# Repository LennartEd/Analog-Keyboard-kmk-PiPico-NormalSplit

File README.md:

# Analog-Keyboard-kmk-PiPico-NormalSplit
This is a fully analog keyboard using magnetic keys and hall sensors. I'm using a RP2040 but since it is KMK (circuitpython) based it should be compatible with other boards. I build a split keyboard, but any type form factor should work. 
This is my first experience with circuitpython so code might me wonky.

#TO-DO
- [ ] automatic callibration
- [ ] support all types of multiplexers (not just 16:1)
- [ ] fix mouse wheel only pressing every second turn

# PCB
**!DONT USE THE PCB PROVIDED!**
The PCB provided has some flaws that make it hard to work with.
**I would recommend making your own PCB and using mine as a template.**
In the future i might create v2 template that fixes the flaws.
Also as LCSC didn't have the LEDs in stock, I build mine without them. So there is no guaranty that I did the LED wiring correctly. I did however test the code with the onboard led of the RP2040, so the code should work.

### Flaws with v1
- Horizontal encoder has the wrong footprint (gnd is not in the middle)
- dont solder MCU daughter board onto PCB directly
- bigger pads for hand soldering
- more mounting holes
- if possible 2 layer PCB for cost saving

### Parts
|Description | Part          | LCSC         |
|:-----------| ------------- |:-------------|
| Hall sensor| HX6659ISO-B   | C495742		|
| Multiplexer| CD74HC4067M96 | C496123		|
| TRRS jack  | PJ-3220-5A	 | C707251		|
| MCU		 | Waveshare RP2040-zero| --	|
| ~~Capacitor 100uF~~| ~~GRM21BR60J107ME15L~~| ~~C141660~~|
|(LED)       |sk6812 mini-e  | C5149201     |

### Part notes
**Hall sensor:** 

**Multiplexer:** Currently any 16to1 Multiplexer should work (giving you 64 keys). If you are not hand soldering i recommend choosing a smaller sized one. Larger (32to1) should also work.

**MCU:** Any circuitpython compatible board should work. You just have to change the footprint on the PCB (which you should do anyway. See "Flaws with v1"

**TRRS jack:** 

**Capacitor:** Capacitors are not strictly necessary but improve resolution. ~~I tried a few and found that 100uF worked the best.~~ Use different sensor filters

#### How it works
The position of the magnet in the switch is red by the hall-effect sensor. Because the pi-pico only has 4 ADCs we need multiplexers to cycle between the sensors. 

# Code
To install the code connect your board and install circuitpython. Then copy the content of the "code" folder into the board. For editing the code you can use Thonny or any text editor.

### pins
To make life easier by not having to use "board.GP.." all the time, create (if not already present) a python file in lib/kmk/quickpin. Then add all the pins (see the other files for reference).
Now when imported with 
~~~
from kmk.quickpin.<boardTypeFolder>.<boardPins> import pinout as pins
~~~
into other files you can just use "pins[x]" to reference pins

### kb.py:
Here you define most variables for you specific board.

### Code.py

### hallCali.py

### analogio.py

# Case

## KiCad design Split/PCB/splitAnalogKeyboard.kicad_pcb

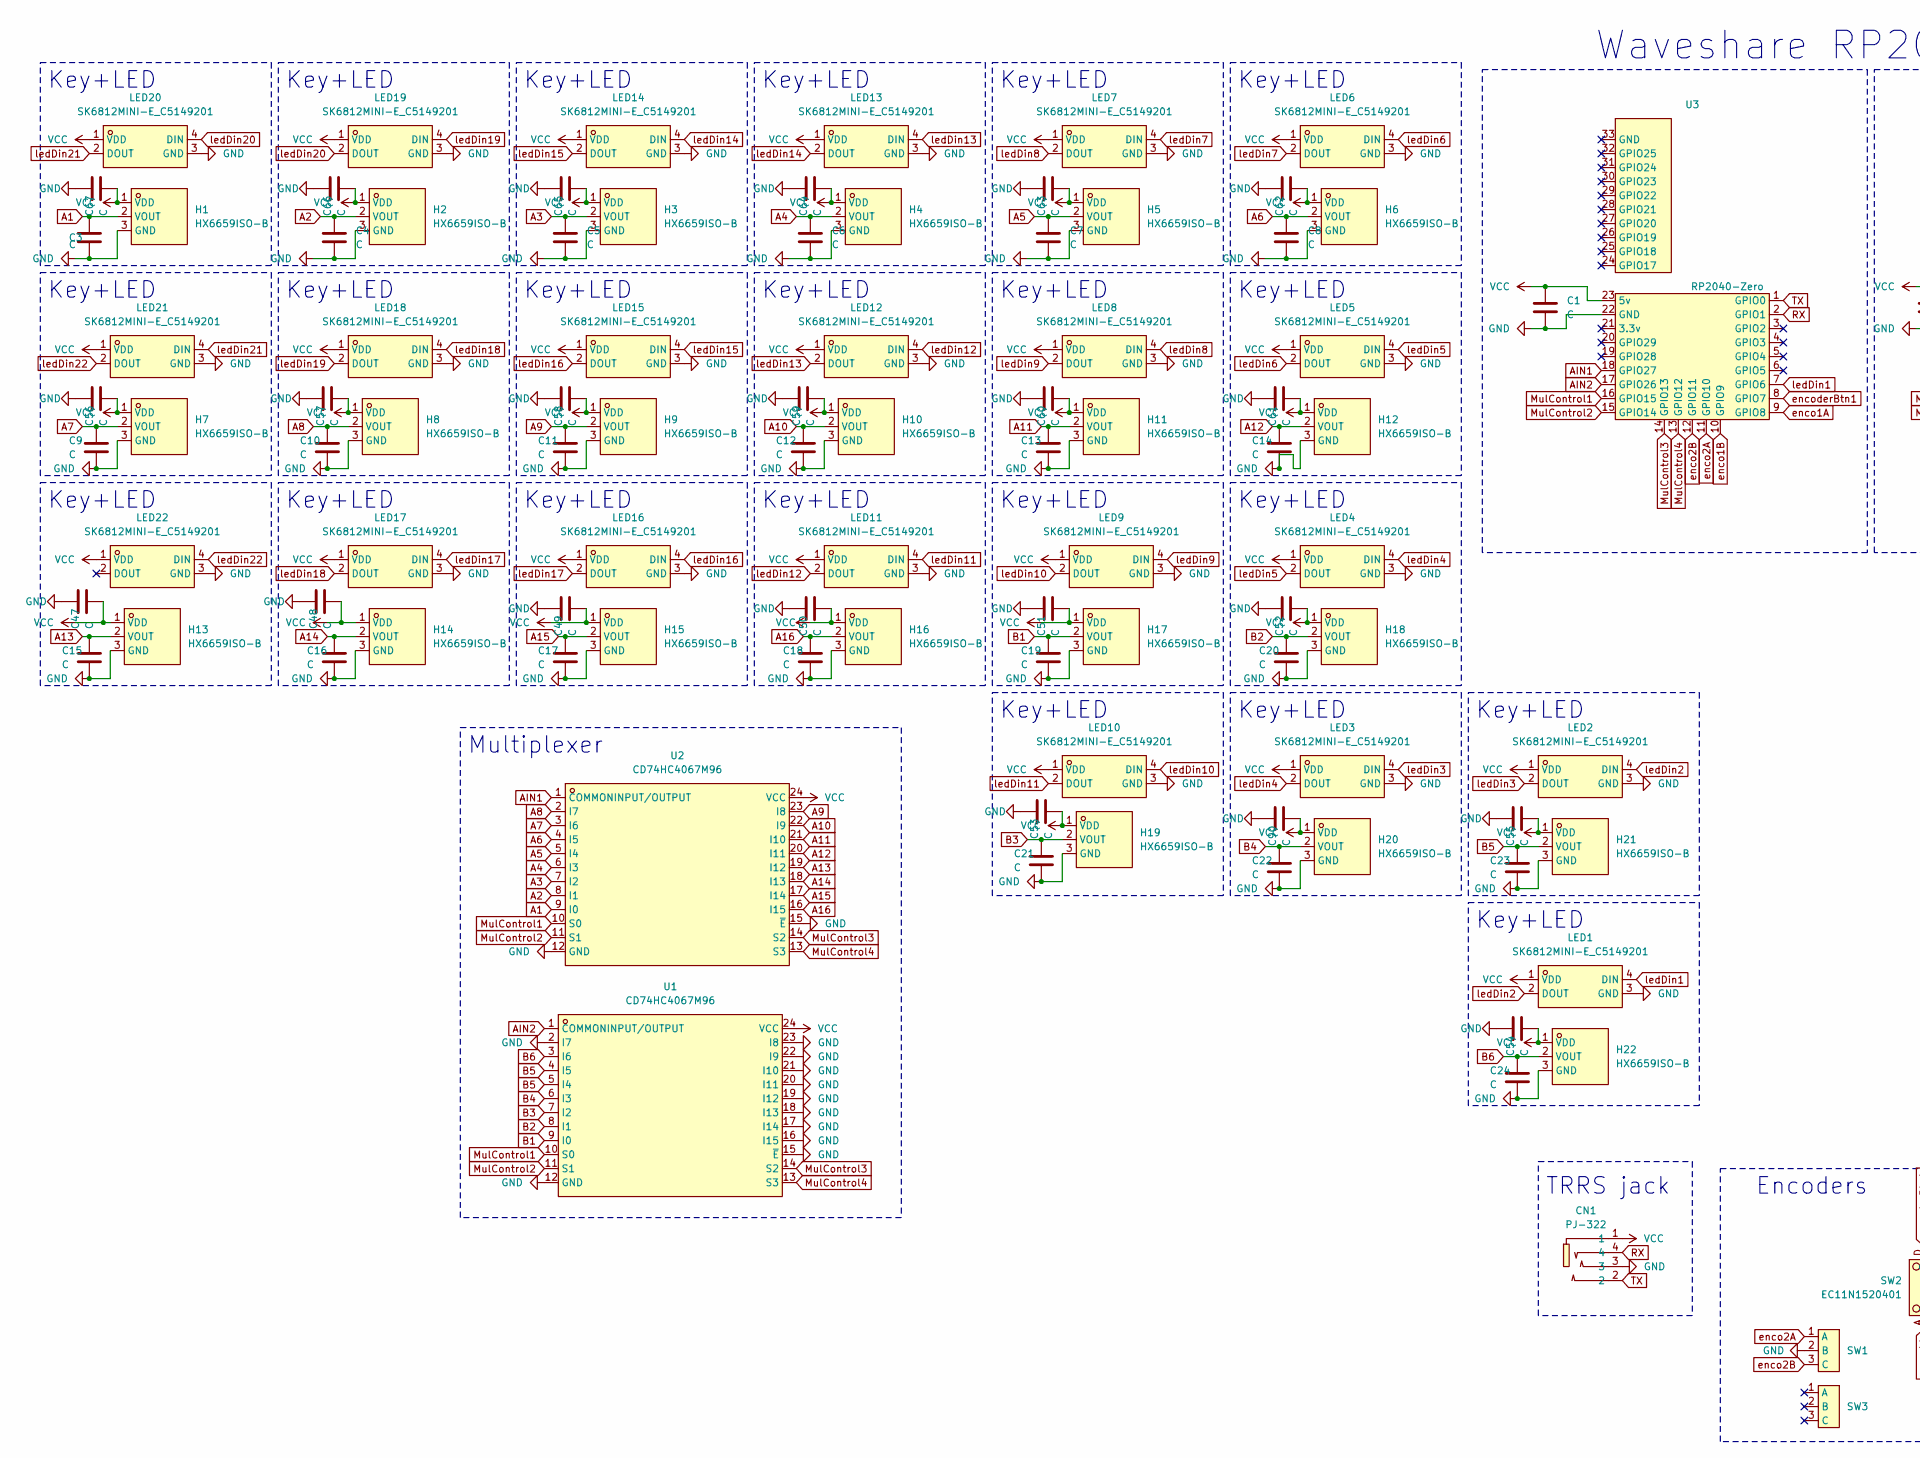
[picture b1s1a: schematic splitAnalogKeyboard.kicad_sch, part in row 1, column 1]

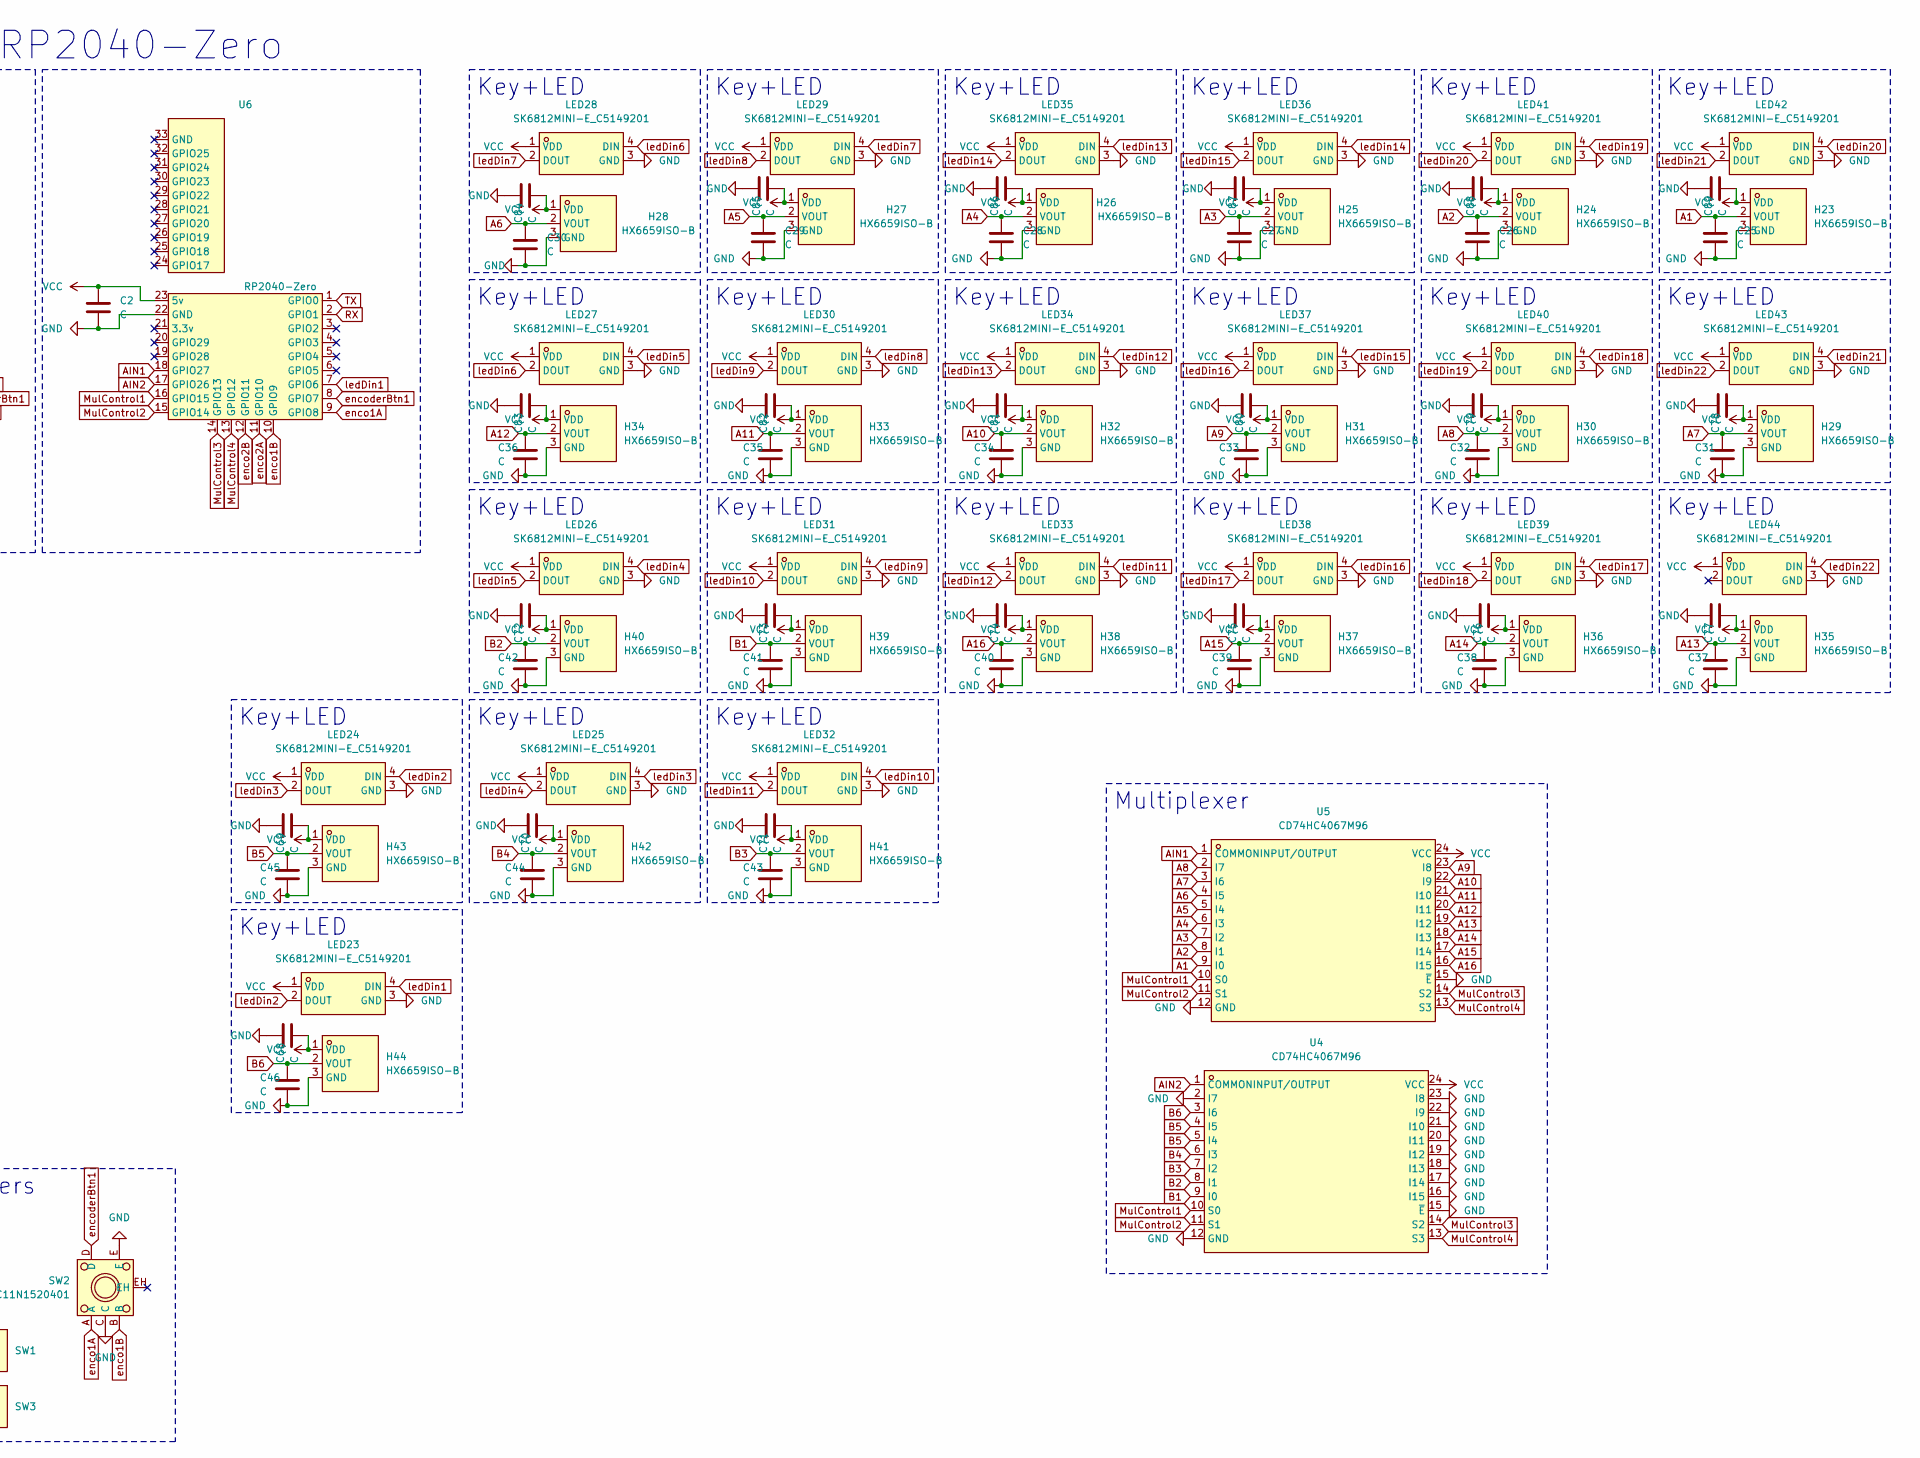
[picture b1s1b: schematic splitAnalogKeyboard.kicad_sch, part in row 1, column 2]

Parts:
C1, C2, C3, C4, C5, C6, C7, C8, C9, C10, C11, C12, C13, C14, C15, C16, C17, C18, C19, C20, C21, C22, C23, C24, C25, C26, C27, C28, C29, C30, C31, C32, C33, C34, C35, C36, C37, C38, C39, C40, C41, C42, C43, C44, C45, C46, C47, C48, C49, C50, C51, C52, C53, C54, C55, C56, C57, C58, C59, C60, C61, C62, C63, C64, C65, C66, C67, C68, C69, C70, C71, C72, C73, C74, C75, C76, C77, C78, C79, C80, C81, C82, C83, C84, C85, C86, C87, C88, C89, C90: C; C_0805_2012Metric_Pad1.18x1.45mm_HandSolder
CN1: PJ-322; AUDIO-TH_HOOYA_PJ-322; LCSC Part C2939185
H1, H2, H3, H4, H5, H6, H7, H8, H9, H10, H11, H12, H13, H14, H15, H16, H17, H18, H19, H20, H21, H22, H23, H24, H25, H26, H27, H28, H29, H30, H31, H32, H33, H34, H35, H36, H37, H38, H39, H40, H41, H42, H43, H44: HX6659ISO-B; SOT-23-3_L2.9-W1.6-P1.90-LS2.8-BR; LCSC Part C495742
LED1, LED2, LED3, LED4, LED5, LED6, LED7, LED8, LED9, LED10, LED11, LED12, LED13, LED14, LED15, LED16, LED17, LED18, LED19, LED20, LED21, LED22, LED23, LED24, LED25, LED26, LED27, LED28, LED29, LED30, LED31, LED32, LED33, LED34, LED35, LED36, LED37, LED38, LED39, LED40, LED41, LED42, LED43, LED44: SK6812MINI-E_C5149201; LED-SMD_L3.2-W2.8-TR; LCSC Part C5149201
SW1, SW3: MouseEncoder
SW2: EC11N1520401; SW-TH_EC11NXXXX; LCSC Part C470703
U1, U2, U4, U5: CD74HC4067M96; SOIC-24_L15.4-W7.5-P1.27-LS10.3-BL; LCSC Part C496123
U3, U6: RP2040-Zero; RP2040-Zero-outer

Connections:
A1: C3.1, C25.1, H1.2 (VOUT), H23.2 (VOUT), U2.9 (I0), U5.9 (I0)
A2: C4.1, C26.1, H2.2 (VOUT), H24.2 (VOUT), U2.8 (I1), U5.8 (I1)
A3: C5.1, C27.1, H3.2 (VOUT), H25.2 (VOUT), U2.7 (I2), U5.7 (I2)
A4: C6.1, C28.1, H4.2 (VOUT), H26.2 (VOUT), U2.6 (I3), U5.6 (I3)
A5: C7.1, C29.1, H5.2 (VOUT), H27.2 (VOUT), U2.5 (I4), U5.5 (I4)
A6: C8.1, C30.1, H6.2 (VOUT), H28.2 (VOUT), U2.4 (I5), U5.4 (I5)
A7: C9.1, C31.1, H7.2 (VOUT), H29.2 (VOUT), U2.3 (I6), U5.3 (I6)
A8: C10.1, C32.1, H8.2 (VOUT), H30.2 (VOUT), U2.2 (I7), U5.2 (I7)
A9: C11.1, C33.1, H9.2 (VOUT), H31.2 (VOUT), U2.23 (I8), U5.23 (I8)
A10: C12.1, C34.1, H10.2 (VOUT), H32.2 (VOUT), U2.22 (I9), U5.22 (I9)
A11: C13.1, C35.1, H11.2 (VOUT), H33.2 (VOUT), U2.21 (I10), U5.21 (I10)
A12: C14.1, C36.1, H12.2 (VOUT), H34.2 (VOUT), U2.20 (I11), U5.20 (I11)
A13: C15.1, C37.1, H13.2 (VOUT), H35.2 (VOUT), U2.19 (I12), U5.19 (I12)
A14: C16.1, C38.1, H14.2 (VOUT), H36.2 (VOUT), U2.18 (I13), U5.18 (I13)
A15: C17.1, C39.1, H15.2 (VOUT), H37.2 (VOUT), U2.17 (I14), U5.17 (I14)
A16: C18.1, C40.1, H16.2 (VOUT), H38.2 (VOUT), U2.16 (I15), U5.16 (I15)
AIN1: U2.1 (COMMONINPUT/OUTPUT), U3.18 (GPIO27), U5.1 (COMMONINPUT/OUTPUT), U6.18 (GPIO27)
AIN2: U1.1 (COMMONINPUT/OUTPUT), U3.17 (GPIO26), U4.1 (COMMONINPUT/OUTPUT), U6.17 (GPIO26)
B1: C19.1, C41.1, H17.2 (VOUT), H39.2 (VOUT), U1.9 (I0), U4.9 (I0)
B2: C20.1, C42.1, H18.2 (VOUT), H40.2 (VOUT), U1.8 (I1), U4.8 (I1)
B3: C21.1, C43.1, H19.2 (VOUT), H41.2 (VOUT), U1.7 (I2), U4.7 (I2)
B4: C22.1, C44.1, H20.2 (VOUT), H42.2 (VOUT), U1.6 (I3), U4.6 (I3)
B5: C23.1, C45.1, H21.2 (VOUT), H43.2 (VOUT), U1.4 (I5), U1.5 (I4), U4.4 (I5), U4.5 (I4)
B6: C24.1, C46.1, H22.2 (VOUT), H44.2 (VOUT), U1.3 (I6), U4.3 (I6)
GND: C1.2, C2.2, C3.2, C4.2, C5.2, C6.2, C7.2, C8.2, C9.2, C10.2, C11.2, C12.2, C13.2, C14.2, C15.2, C16.2, C17.2, C18.2, C19.2, C20.2, C21.2, C22.2, C23.2, C24.2, C25.2, C26.2, C27.2, C28.2, C29.2, C30.2, C31.2, C32.2, C33.2, C34.2, C35.2, C36.2, C37.2, C38.2, C39.2, C40.2, C41.2, C42.2, C43.2, C44.2, C45.2, C46.2, C47.1, C48.1, C49.1, C50.1, C51.1, C52.1, C53.1, C54.1, C55.1, C56.1, C57.1, C58.1, C59.1, C60.1, C61.1, C62.1, C63.1, C64.1, C65.1, C66.1, C67.1, C68.1, C69.1, C70.1, C71.1, C72.1, C73.1, C74.1, C75.1, C76.1, C77.1, C78.1, C79.1, C80.1, C81.1, C82.1, C83.1, C84.1, C85.1, C86.1, C87.1, C88.1, C89.1, C90.1, CN1.3, H1.3 (GND), H2.3 (GND), H3.3 (GND), H4.3 (GND), H5.3 (GND), H6.3 (GND), H7.3 (GND), H8.3 (GND), H9.3 (GND), H10.3 (GND), H11.3 (GND), H12.3 (GND), H13.3 (GND), H14.3 (GND), H15.3 (GND), H16.3 (GND), H17.3 (GND), H18.3 (GND), H19.3 (GND), H20.3 (GND), H21.3 (GND), H22.3 (GND), H23.3 (GND), H24.3 (GND), H25.3 (GND), H26.3 (GND), H27.3 (GND), H28.3 (GND), H29.3 (GND), H30.3 (GND), H31.3 (GND), H32.3 (GND), H33.3 (GND), H34.3 (GND), H35.3 (GND), H36.3 (GND), H37.3 (GND), H38.3 (GND), H39.3 (GND), H40.3 (GND), H41.3 (GND), H42.3 (GND), H43.3 (GND), H44.3 (GND), LED1.3 (GND), LED2.3 (GND), LED3.3 (GND), LED4.3 (GND), LED5.3 (GND), LED6.3 (GND), LED7.3 (GND), LED8.3 (GND), LED9.3 (GND), LED10.3 (GND), LED11.3 (GND), LED12.3 (GND), LED13.3 (GND), LED14.3 (GND), LED15.3 (GND), LED16.3 (GND), LED17.3 (GND), LED18.3 (GND), LED19.3 (GND), LED20.3 (GND), LED21.3 (GND), LED22.3 (GND), LED23.3 (GND), LED24.3 (GND), LED25.3 (GND), LED26.3 (GND), LED27.3 (GND), LED28.3 (GND), LED29.3 (GND), LED30.3 (GND), LED31.3 (GND), LED32.3 (GND), LED33.3 (GND), LED34.3 (GND), LED35.3 (GND), LED36.3 (GND), LED37.3 (GND), LED38.3 (GND), LED39.3 (GND), LED40.3 (GND), LED41.3 (GND), LED42.3 (GND), LED43.3 (GND), LED44.3 (GND), SW1.2 (B), SW2.C, SW2.E, U1.2 (I7), U1.12 (GND), U1.15 (~E), U1.16 (I15), U1.17 (I14), U1.18 (I13), U1.19 (I12), U1.20 (I11), U1.21 (I10), U1.22 (I9), U1.23 (I8), U2.12 (GND), U2.15 (~E), U3.22 (GND), U4.2 (I7), U4.12 (GND), U4.15 (~E), U4.16 (I15), U4.17 (I14), U4.18 (I13), U4.19 (I12), U4.20 (I11), U4.21 (I10), U4.22 (I9), U4.23 (I8), U5.12 (GND), U5.15 (~E), U6.22 (GND)
MulControl1: U1.10 (S0), U2.10 (S0), U3.16 (GPIO15), U4.10 (S0), U5.10 (S0), U6.16 (GPIO15)
MulControl2: U1.11 (S1), U2.11 (S1), U3.15 (GPIO14), U4.11 (S1), U5.11 (S1), U6.15 (GPIO14)
MulControl3: U1.14 (S2), U2.14 (S2), U3.14 (GPIO13), U4.14 (S2), U5.14 (S2), U6.14 (GPIO13)
MulControl4: U1.13 (S3), U2.13 (S3), U3.13 (GPIO12), U4.13 (S3), U5.13 (S3), U6.13 (GPIO12)
RX: CN1.4, U3.2 (GPIO1), U6.2 (GPIO1)
TX: CN1.2, U3.1 (GPIO0), U6.1 (GPIO0)
VCC: C1.1, C2.1, C47.2, C48.2, C49.2, C50.2, C51.2, C52.2, C53.2, C54.2, C55.2, C56.2, C57.2, C58.2, C59.2, C60.2, C61.2, C62.2, C63.2, C64.2, C65.2, C66.2, C67.2, C68.2, C69.2, C70.2, C71.2, C72.2, C73.2, C74.2, C75.2, C76.2, C77.2, C78.2, C79.2, C80.2, C81.2, C82.2, C83.2, C84.2, C85.2, C86.2, C87.2, C88.2, C89.2, C90.2, CN1.1, H1.1 (VDD), H2.1 (VDD), H3.1 (VDD), H4.1 (VDD), H5.1 (VDD), H6.1 (VDD), H7.1 (VDD), H8.1 (VDD), H9.1 (VDD), H10.1 (VDD), H11.1 (VDD), H12.1 (VDD), H13.1 (VDD), H14.1 (VDD), H15.1 (VDD), H16.1 (VDD), H17.1 (VDD), H18.1 (VDD), H19.1 (VDD), H20.1 (VDD), H21.1 (VDD), H22.1 (VDD), H23.1 (VDD), H24.1 (VDD), H25.1 (VDD), H26.1 (VDD), H27.1 (VDD), H28.1 (VDD), H29.1 (VDD), H30.1 (VDD), H31.1 (VDD), H32.1 (VDD), H33.1 (VDD), H34.1 (VDD), H35.1 (VDD), H36.1 (VDD), H37.1 (VDD), H38.1 (VDD), H39.1 (VDD), H40.1 (VDD), H41.1 (VDD), H42.1 (VDD), H43.1 (VDD), H44.1 (VDD), LED1.1 (VDD), LED2.1 (VDD), LED3.1 (VDD), LED4.1 (VDD), LED5.1 (VDD), LED6.1 (VDD), LED7.1 (VDD), LED8.1 (VDD), LED9.1 (VDD), LED10.1 (VDD), LED11.1 (VDD), LED12.1 (VDD), LED13.1 (VDD), LED14.1 (VDD), LED15.1 (VDD), LED16.1 (VDD), LED17.1 (VDD), LED18.1 (VDD), LED19.1 (VDD), LED20.1 (VDD), LED21.1 (VDD), LED22.1 (VDD), LED23.1 (VDD), LED24.1 (VDD), LED25.1 (VDD), LED26.1 (VDD), LED27.1 (VDD), LED28.1 (VDD), LED29.1 (VDD), LED30.1 (VDD), LED31.1 (VDD), LED32.1 (VDD), LED33.1 (VDD), LED34.1 (VDD), LED35.1 (VDD), LED36.1 (VDD), LED37.1 (VDD), LED38.1 (VDD), LED39.1 (VDD), LED40.1 (VDD), LED41.1 (VDD), LED42.1 (VDD), LED43.1 (VDD), LED44.1 (VDD), U1.24 (VCC), U2.24 (VCC), U3.23 (5v), U4.24 (VCC), U5.24 (VCC), U6.23 (5v)
enco1A: SW2.A, U3.9 (GPIO8), U6.9 (GPIO8)
enco1B: SW2.B, U3.10 (GPIO9), U6.10 (GPIO9)
enco2A: SW1.1 (A), U3.11 (GPIO10), U6.11 (GPIO10)
enco2B: SW1.3 (C), U3.12 (GPIO11), U6.12 (GPIO11)
encoderBtn1: SW2.D, U3.8 (GPIO7), U6.8 (GPIO7)
ledDin1: LED1.4 (DIN), LED23.4 (DIN), U3.7 (GPIO6), U6.7 (GPIO6)
ledDin2: LED1.2 (DOUT), LED2.4 (DIN), LED23.2 (DOUT), LED24.4 (DIN)
ledDin3: LED2.2 (DOUT), LED3.4 (DIN), LED24.2 (DOUT), LED25.4 (DIN)
ledDin4: LED3.2 (DOUT), LED4.4 (DIN), LED25.2 (DOUT), LED26.4 (DIN)
ledDin5: LED4.2 (DOUT), LED5.4 (DIN), LED26.2 (DOUT), LED27.4 (DIN)
ledDin6: LED5.2 (DOUT), LED6.4 (DIN), LED27.2 (DOUT), LED28.4 (DIN)
ledDin7: LED6.2 (DOUT), LED7.4 (DIN), LED28.2 (DOUT), LED29.4 (DIN)
ledDin8: LED7.2 (DOUT), LED8.4 (DIN), LED29.2 (DOUT), LED30.4 (DIN)
ledDin9: LED8.2 (DOUT), LED9.4 (DIN), LED30.2 (DOUT), LED31.4 (DIN)
ledDin10: LED9.2 (DOUT), LED10.4 (DIN), LED31.2 (DOUT), LED32.4 (DIN)
ledDin11: LED10.2 (DOUT), LED11.4 (DIN), LED32.2 (DOUT), LED33.4 (DIN)
ledDin12: LED11.2 (DOUT), LED12.4 (DIN), LED33.2 (DOUT), LED34.4 (DIN)
ledDin13: LED12.2 (DOUT), LED13.4 (DIN), LED34.2 (DOUT), LED35.4 (DIN)
ledDin14: LED13.2 (DOUT), LED14.4 (DIN), LED35.2 (DOUT), LED36.4 (DIN)
ledDin15: LED14.2 (DOUT), LED15.4 (DIN), LED36.2 (DOUT), LED37.4 (DIN)
ledDin16: LED15.2 (DOUT), LED16.4 (DIN), LED37.2 (DOUT), LED38.4 (DIN)
ledDin17: LED16.2 (DOUT), LED17.4 (DIN), LED38.2 (DOUT), LED39.4 (DIN)
ledDin18: LED17.2 (DOUT), LED18.4 (DIN), LED39.2 (DOUT), LED40.4 (DIN)
ledDin19: LED18.2 (DOUT), LED19.4 (DIN), LED40.2 (DOUT), LED41.4 (DIN)
ledDin20: LED19.2 (DOUT), LED20.4 (DIN), LED41.2 (DOUT), LED42.4 (DIN)
ledDin21: LED20.2 (DOUT), LED21.4 (DIN), LED42.2 (DOUT), LED43.4 (DIN)
ledDin22: LED21.2 (DOUT), LED22.4 (DIN), LED43.2 (DOUT), LED44.4 (DIN)

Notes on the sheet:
Key+LED
Multiplexer
Encoders
Waveshare RP2040-Zero
TRRS jack

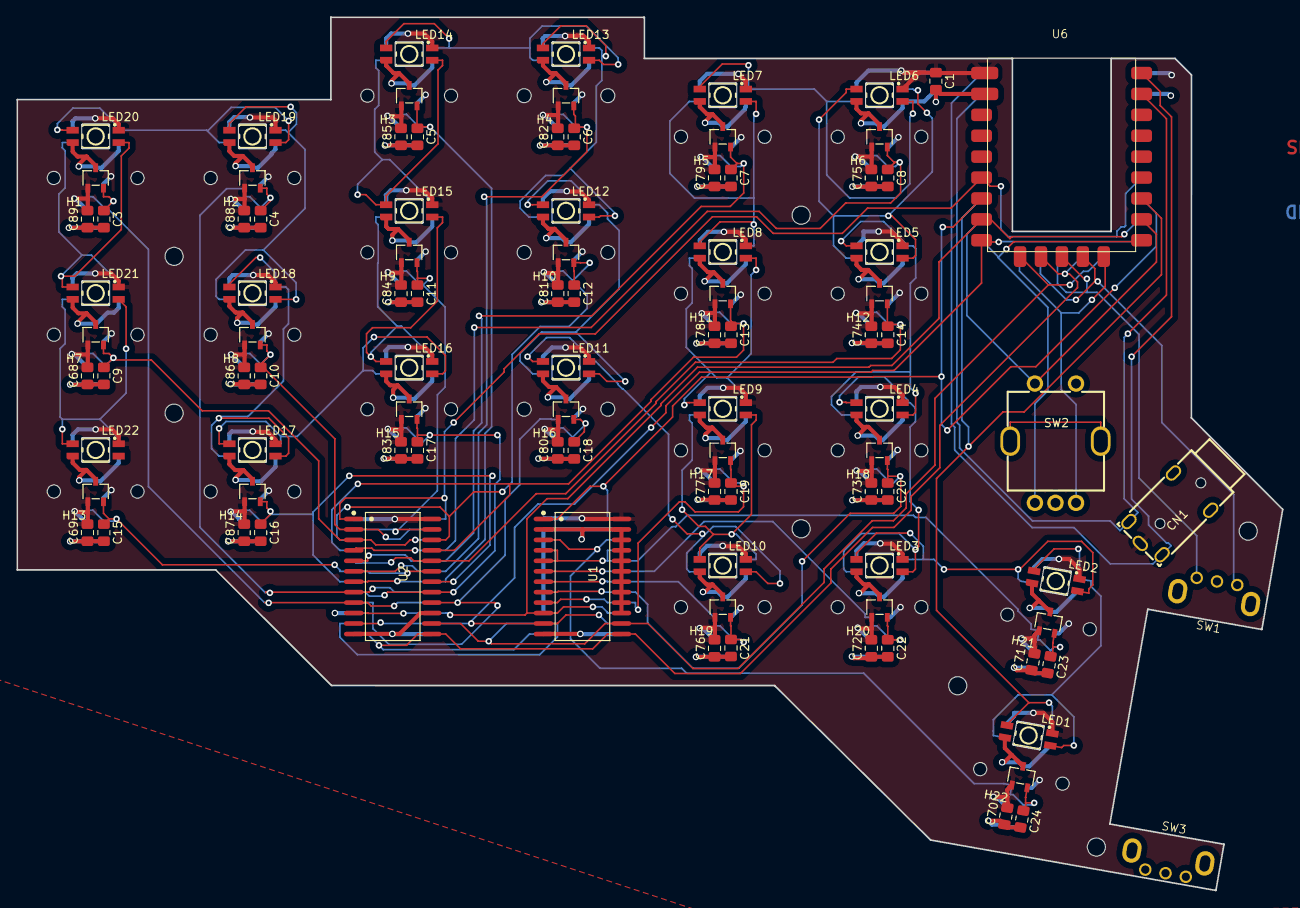
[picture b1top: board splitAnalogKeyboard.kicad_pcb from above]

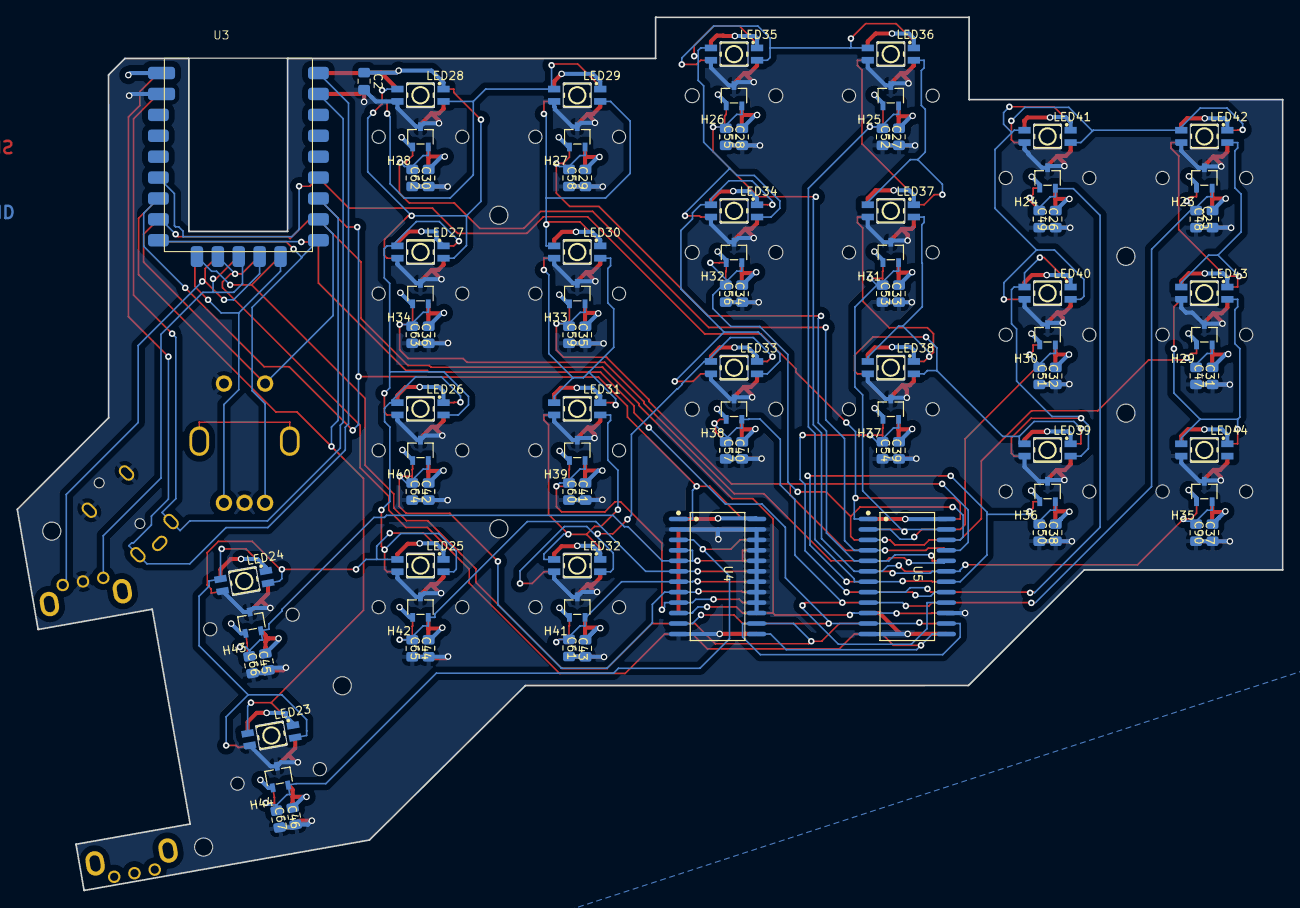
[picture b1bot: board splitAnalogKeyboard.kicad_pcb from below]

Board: 4 copper layers, 153.8 x 106.1 mm, 188 parts (92 on the bottom side), 59 nets.

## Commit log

2023-08-24 Update README.md
    test
2023-08-24 Roadmap
2023-08-24 spelling
2023-08-24 more
2023-08-24 base code Normal
2023-08-24 moved code to folder
2023-09-26 split code upload
2023-09-26 analogio scanner added
2023-09-26 analogio scanner
2023-09-27 update roadmap
2023-10-06 rapid trigger added
2023-10-21 cleanup + comments
2023-10-24 test pcb
2023-10-27 Split documentaition
2023-11-10 uart flip false,attrib change
2023-11-10 layers working
2023-11-11 basic qwerty+nuber+wasd layers added
2023-12-15 rapidTrigger changes to not get stuck
2023-12-15 rapidTrigger fix
2023-12-15 add image
2023-12-15 new readme
2023-12-15 +PCB&code
2023-12-25 Parts
2024-01-15 boot.py added
2024-02-07 keymap changes
2024-02-07 Readme TO-DO added
2024-02-07 first auto range test
2024-02-07 working auto calibration
2024-02-07 auto calibration working
2024-02-07 fixes
2024-03-08 horizontal encoder error
2024-10-04 Dont use my filters
